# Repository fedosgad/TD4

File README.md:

# TD4
Schematics, PCBs and SystemVerilog simulation for extended version of TD4 CPU.

All circuit-related work done in KiCad.

Verilog file are (will be) under verilog/ folder

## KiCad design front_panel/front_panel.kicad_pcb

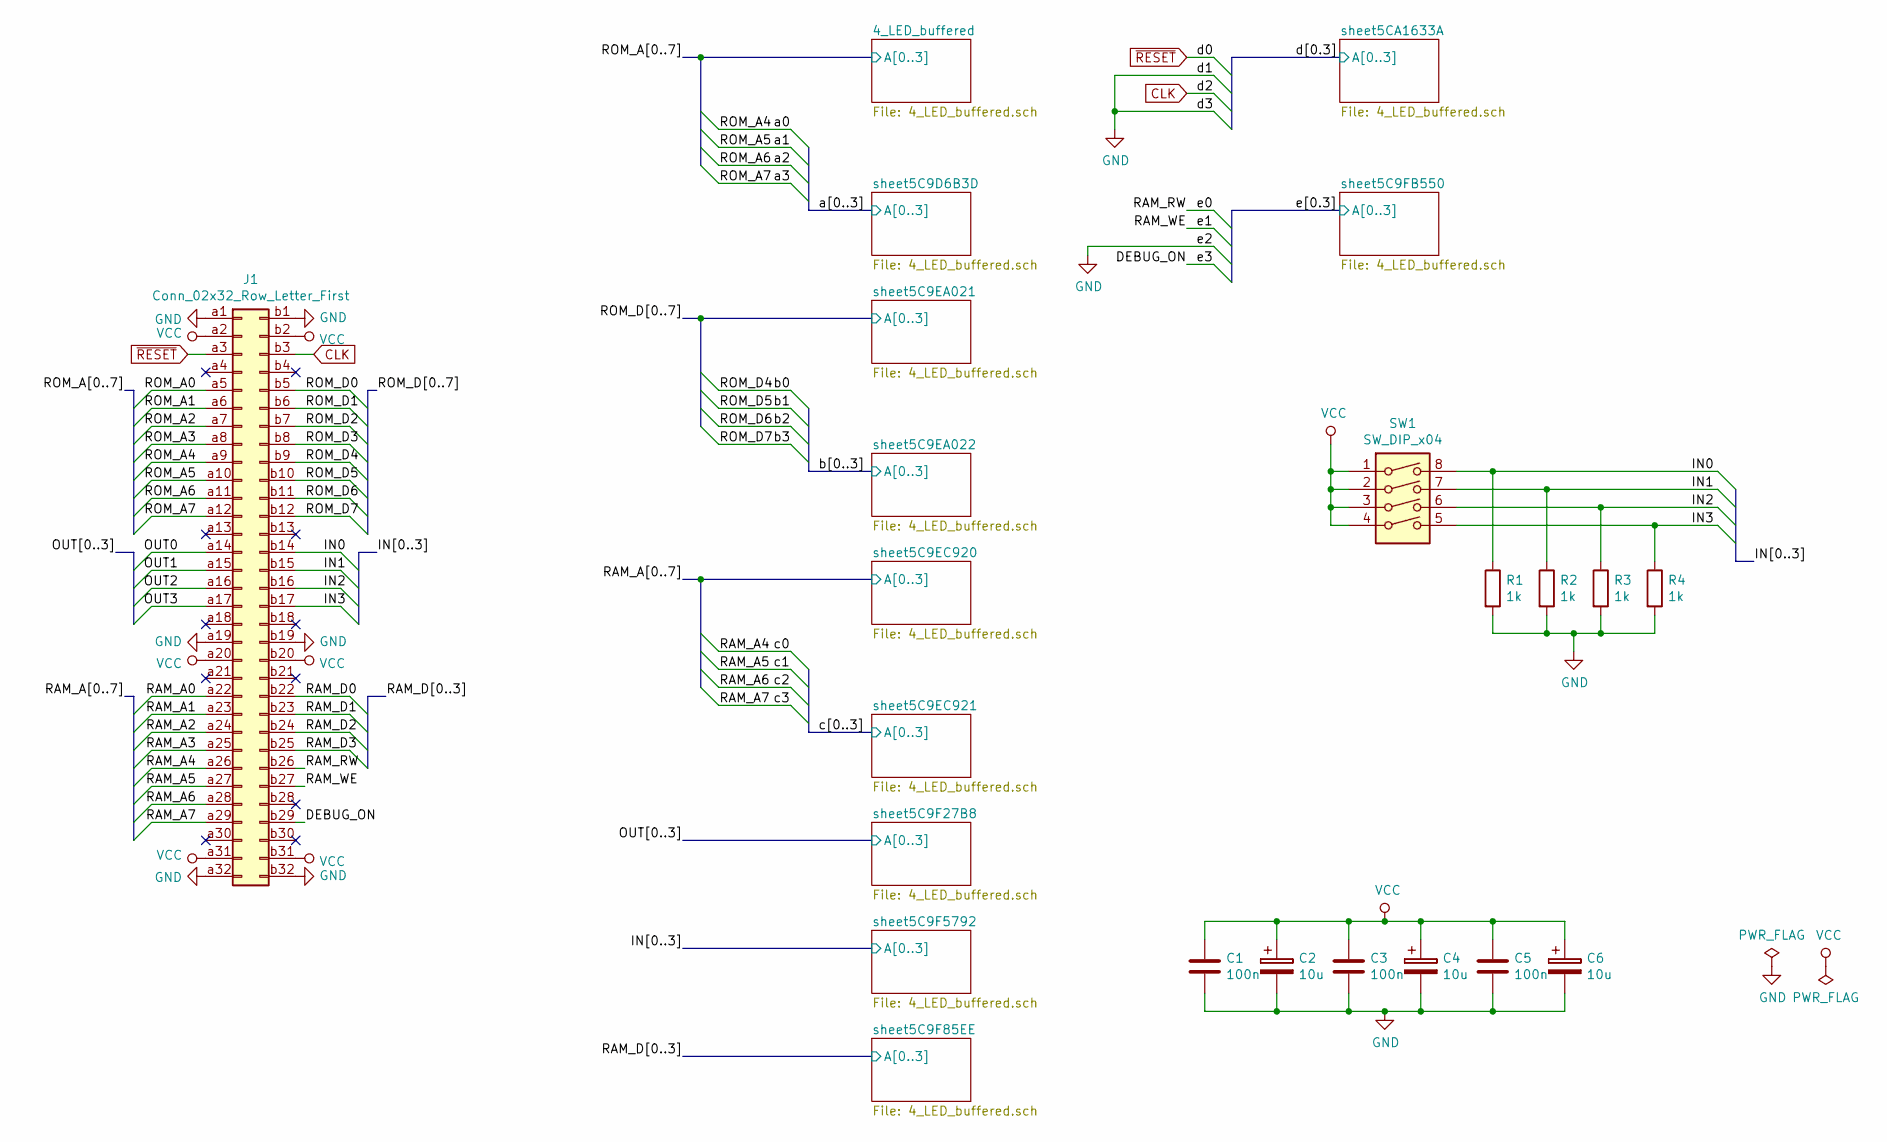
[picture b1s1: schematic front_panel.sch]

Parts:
C1, C3, C5: 100n; C_0805_2012Metric
C2, C4, C6: 10u; CP_EIA-3216-18_Kemet-A
J1: Conn_02x32_Row_Letter_First; DIN41612_B_2x32_Horizontal
R1, R2, R3, R4: 1k; R_0805_2012Metric
SW1: SW_DIP_x04; SW_DIP_SPSTx04_Slide_9.78x12.34mm_W7.62mm_P2.54mm

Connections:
/DEBUG_ON: J1.b29; also elsewhere on the board
/IN0: J1.b14, R1.1, SW1.8; also elsewhere on the board
/IN1: J1.b15, R2.1, SW1.7; also elsewhere on the board
/IN2: J1.b16, R3.1, SW1.6; also elsewhere on the board
/IN3: J1.b17, R4.1, SW1.5; also elsewhere on the board
/OUT0: J1.a14; also elsewhere on the board
/OUT1: J1.a15; also elsewhere on the board
/OUT2: J1.a16; also elsewhere on the board
/OUT3: J1.a17; also elsewhere on the board
/RAM_A0: J1.a22; also elsewhere on the board
/RAM_A1: J1.a23; also elsewhere on the board
/RAM_A2: J1.a24; also elsewhere on the board
/RAM_A3: J1.a25; also elsewhere on the board
/RAM_A4: J1.a26; also elsewhere on the board
/RAM_A5: J1.a27; also elsewhere on the board
/RAM_A6: J1.a28; also elsewhere on the board
/RAM_A7: J1.a29; also elsewhere on the board
/RAM_D0: J1.b22; also elsewhere on the board
/RAM_D1: J1.b23; also elsewhere on the board
/RAM_D2: J1.b24; also elsewhere on the board
/RAM_D3: J1.b25; also elsewhere on the board
/RAM_RW: J1.b26; also elsewhere on the board
/RAM_WE: J1.b27; also elsewhere on the board
/ROM_A0: J1.a5; also elsewhere on the board
/ROM_A1: J1.a6; also elsewhere on the board
/ROM_A2: J1.a7; also elsewhere on the board
/ROM_A3: J1.a8; also elsewhere on the board
/ROM_A4: J1.a9; also elsewhere on the board
/ROM_A5: J1.a10; also elsewhere on the board
/ROM_A6: J1.a11; also elsewhere on the board
/ROM_A7: J1.a12; also elsewhere on the board
/ROM_D0: J1.b5; also elsewhere on the board
/ROM_D1: J1.b6; also elsewhere on the board
/ROM_D2: J1.b7; also elsewhere on the board
/ROM_D3: J1.b8; also elsewhere on the board
/ROM_D4: J1.b9; also elsewhere on the board
/ROM_D5: J1.b10; also elsewhere on the board
/ROM_D6: J1.b11; also elsewhere on the board
/ROM_D7: J1.b12; also elsewhere on the board
CLK: J1.b3; also elsewhere on the board
GND: C1.2, C2.2, C3.2, C4.2, C5.2, C6.2, J1.a1, J1.a19, J1.a32, J1.b1, J1.b19, J1.b32, R1.2, R2.2, R3.2, R4.2; also elsewhere on the board
VCC: C1.1, C2.1, C3.1, C4.1, C5.1, C6.1, J1.a2, J1.a20, J1.a31, J1.b2, J1.b20, J1.b31, SW1.1, SW1.2, SW1.3, SW1.4; also elsewhere on the board
~RESET: J1.a3; also elsewhere on the board

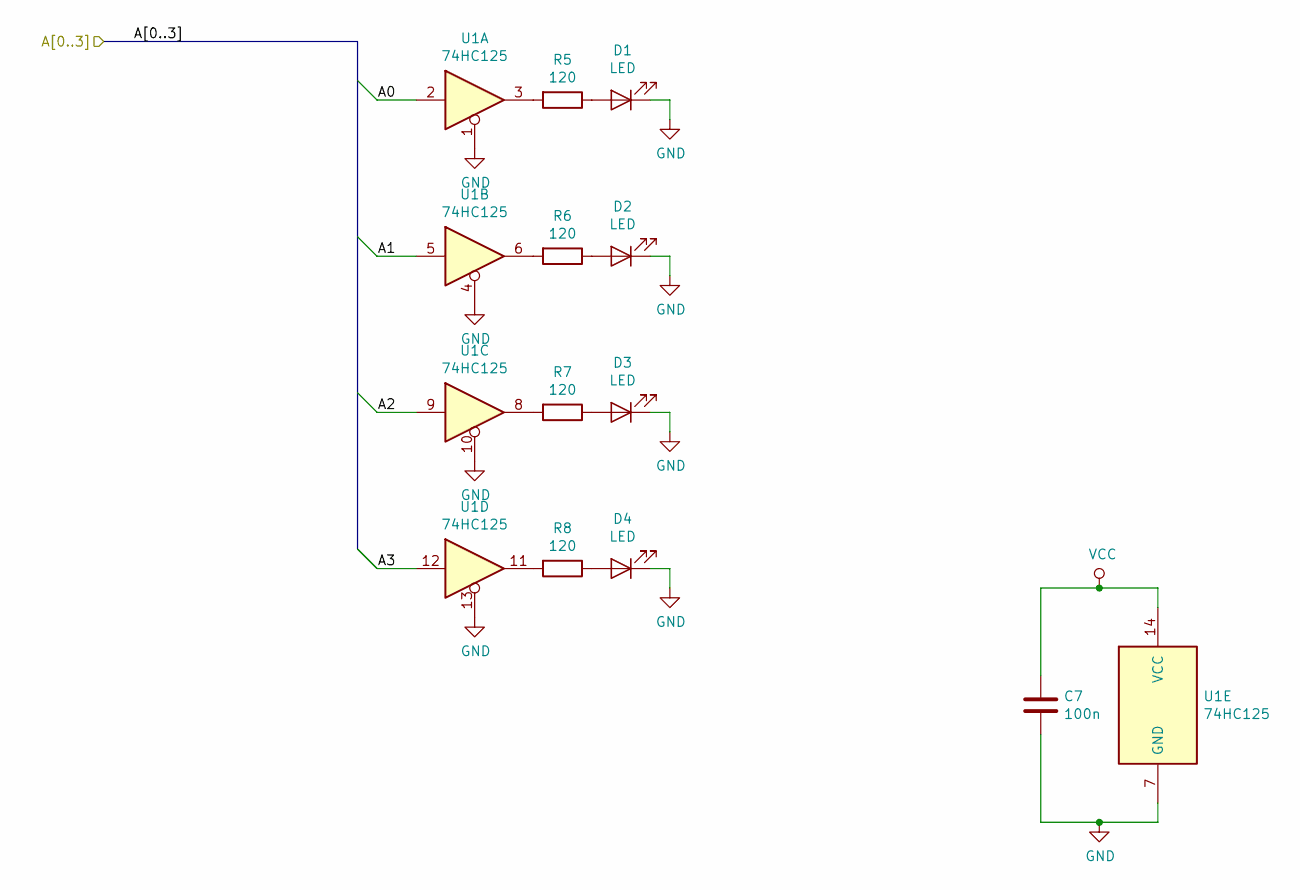
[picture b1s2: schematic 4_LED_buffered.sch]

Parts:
C7: 100n; C_0805_2012Metric
D1, D2, D3, D4: LED; LED_D5.0mm
R5, R6, R7, R8: 120; R_0805_2012Metric
U1: 74HC125; SOIC-14_3.9x8.7mm_P1.27mm

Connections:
/ROM_A0: U1.2; also elsewhere on the board
/ROM_A1: U1.5; also elsewhere on the board
/ROM_A2: U1.9; also elsewhere on the board
/ROM_A3: U1.12; also elsewhere on the board
GND: C7.2, D1.1 (K), D2.1 (K), D3.1 (K), D4.1 (K), U1.1, U1.4, U1.7 (GND), U1.10, U1.13; also elsewhere on the board
unnamed: D1.2 (A), R5.1
unnamed: D2.2 (A), R6.1
unnamed: D3.2 (A), R7.1
unnamed: D4.2 (A), R8.1
unnamed: R5.2, U1.3
unnamed: R6.2, U1.6
unnamed: R7.2, U1.8
unnamed: R8.2, U1.11
VCC: C7.1, U1.14 (VCC); also elsewhere on the board

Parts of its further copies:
C8, C9, C10, C11, C12, C13, C14, C15, C16, C17: 100n; C_0805_2012Metric
D5, D6, D7, D8, D9, D10, D11, D12, D13, D14, D15, D16, D17, D18, D19, D20, D21, D22, D23, D24, D25, D26, D27, D28, D29, D30, D31, D32, D33, D34, D35, D36, D37, D38, D39, D40, D41, D42, D43, D44: LED; LED_D5.0mm
R9, R10, R11, R12, R13, R14, R15, R16, R17, R18, R19, R20, R21, R22, R23, R24, R25, R26, R27, R28, R29, R30, R31, R32, R33, R34, R35, R36, R37, R38, R39, R40, R41, R42, R43, R44, R45, R46, R47, R48: 120; R_0805_2012Metric
U2, U3, U4, U5, U6, U7, U8, U9, U10, U11: 74HC125; SOIC-14_3.9x8.7mm_P1.27mm

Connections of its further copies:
/DEBUG_ON: U10.12; also elsewhere on the board
/IN0: U8.2; also elsewhere on the board
/IN1: U8.5; also elsewhere on the board
/IN2: U8.9; also elsewhere on the board
/IN3: U8.12; also elsewhere on the board
/OUT0: U7.2; also elsewhere on the board
/OUT1: U7.5; also elsewhere on the board
/OUT2: U7.9; also elsewhere on the board
/OUT3: U7.12; also elsewhere on the board
/RAM_A0: U5.2; also elsewhere on the board
/RAM_A1: U5.5; also elsewhere on the board
/RAM_A2: U5.9; also elsewhere on the board
/RAM_A3: U5.12; also elsewhere on the board
/RAM_A4: U6.2; also elsewhere on the board
/RAM_A5: U6.5; also elsewhere on the board
/RAM_A6: U6.9; also elsewhere on the board
/RAM_A7: U6.12; also elsewhere on the board
/RAM_D0: U9.2; also elsewhere on the board
/RAM_D1: U9.5; also elsewhere on the board
/RAM_D2: U9.9; also elsewhere on the board
/RAM_D3: U9.12; also elsewhere on the board
/RAM_RW: U10.2; also elsewhere on the board
/RAM_WE: U10.5; also elsewhere on the board
/ROM_A4: U2.2; also elsewhere on the board
/ROM_A5: U2.5; also elsewhere on the board
/ROM_A6: U2.9; also elsewhere on the board
/ROM_A7: U2.12; also elsewhere on the board
/ROM_D0: U3.2; also elsewhere on the board
/ROM_D1: U3.5; also elsewhere on the board
/ROM_D2: U3.9; also elsewhere on the board
/ROM_D3: U3.12; also elsewhere on the board
/ROM_D4: U4.2; also elsewhere on the board
/ROM_D5: U4.5; also elsewhere on the board
/ROM_D6: U4.9; also elsewhere on the board
/ROM_D7: U4.12; also elsewhere on the board
CLK: U11.9; also elsewhere on the board
GND: C8.2, C9.2, C10.2, C11.2, C12.2, C13.2, C14.2, C15.2, C16.2, C17.2, D5.1 (K), D6.1 (K), D7.1 (K), D8.1 (K), D9.1 (K), D10.1 (K), D11.1 (K), D12.1 (K), D13.1 (K), D14.1 (K), D15.1 (K), D16.1 (K), D17.1 (K), D18.1 (K), D19.1 (K), D20.1 (K), D21.1 (K), D22.1 (K), D23.1 (K), D24.1 (K), D25.1 (K), D26.1 (K), D27.1 (K), D28.1 (K), D29.1 (K), D30.1 (K), D31.1 (K), D32.1 (K), D33.1 (K), D34.1 (K), D35.1 (K), D36.1 (K), D37.1 (K), D38.1 (K), D39.1 (K), D40.1 (K), D41.1 (K), D42.1 (K), D43.1 (K), D44.1 (K), U2.1, U2.4, U2.7 (GND), U2.10, U2.13, U3.1, U3.4, U3.7 (GND), U3.10, U3.13, U4.1, U4.4, U4.7 (GND), U4.10, U4.13, U5.1, U5.4, U5.7 (GND), U5.10, U5.13, U6.1, U6.4, U6.7 (GND), U6.10, U6.13, U7.1, U7.4, U7.7 (GND), U7.10, U7.13, U8.1, U8.4, U8.7 (GND), U8.10, U8.13, U9.1, U9.4, U9.7 (GND), U9.10, U9.13, U10.1, U10.4, U10.7 (GND), U10.9, U10.10, U10.13, U11.1, U11.4, U11.5, U11.7 (GND), U11.10, U11.12, U11.13; also elsewhere on the board
unnamed: D5.2 (A), R9.1
unnamed: D6.2 (A), R10.1
unnamed: D7.2 (A), R11.1
unnamed: D8.2 (A), R12.1
unnamed: D9.2 (A), R13.1
unnamed: D10.2 (A), R14.1
unnamed: D11.2 (A), R15.1
unnamed: D12.2 (A), R16.1
unnamed: D13.2 (A), R17.1
unnamed: D14.2 (A), R18.1
unnamed: D15.2 (A), R19.1
unnamed: D16.2 (A), R20.1
unnamed: D17.2 (A), R21.1
unnamed: D18.2 (A), R22.1
unnamed: D19.2 (A), R23.1
unnamed: D20.2 (A), R24.1
unnamed: D21.2 (A), R25.1
unnamed: D22.2 (A), R26.1
unnamed: D23.2 (A), R27.1
unnamed: D24.2 (A), R28.1
unnamed: D25.2 (A), R29.1
unnamed: D26.2 (A), R30.1
unnamed: D27.2 (A), R31.1
unnamed: D28.2 (A), R32.1
unnamed: D29.2 (A), R33.1
unnamed: D30.2 (A), R34.1
unnamed: D31.2 (A), R35.1
unnamed: D32.2 (A), R36.1
unnamed: D33.2 (A), R37.1
unnamed: D34.2 (A), R38.1
unnamed: D35.2 (A), R39.1
unnamed: D36.2 (A), R40.1
unnamed: D37.2 (A), R41.1
unnamed: D38.2 (A), R42.1
unnamed: D39.2 (A), R43.1
unnamed: D40.2 (A), R44.1
unnamed: D41.2 (A), R45.1
unnamed: D42.2 (A), R46.1
unnamed: D43.2 (A), R47.1
unnamed: D44.2 (A), R48.1
unnamed: R9.2, U2.3
unnamed: R10.2, U2.6
unnamed: R11.2, U2.8
unnamed: R12.2, U2.11
unnamed: R13.2, U3.3
unnamed: R14.2, U3.6
unnamed: R15.2, U3.8
unnamed: R16.2, U3.11
unnamed: R17.2, U4.3
unnamed: R18.2, U4.6
unnamed: R19.2, U4.8
unnamed: R20.2, U4.11
unnamed: R21.2, U5.3
unnamed: R22.2, U5.6
unnamed: R23.2, U5.8
unnamed: R24.2, U5.11
unnamed: R25.2, U6.3
unnamed: R26.2, U6.6
unnamed: R27.2, U6.8
unnamed: R28.2, U6.11
unnamed: R29.2, U7.3
unnamed: R30.2, U7.6
unnamed: R31.2, U7.8
unnamed: R32.2, U7.11
unnamed: R33.2, U8.3
unnamed: R34.2, U8.6
unnamed: R35.2, U8.8
unnamed: R36.2, U8.11
unnamed: R37.2, U9.3
unnamed: R38.2, U9.6
unnamed: R39.2, U9.8
unnamed: R40.2, U9.11
unnamed: R41.2, U10.3
unnamed: R42.2, U10.6
unnamed: R43.2, U10.8
unnamed: R44.2, U10.11
unnamed: R45.2, U11.3
unnamed: R46.2, U11.6
unnamed: R47.2, U11.8
unnamed: R48.2, U11.11
VCC: C8.1, C9.1, C10.1, C11.1, C12.1, C13.1, C14.1, C15.1, C16.1, C17.1, U2.14 (VCC), U3.14 (VCC), U4.14 (VCC), U5.14 (VCC), U6.14 (VCC), U7.14 (VCC), U8.14 (VCC), U9.14 (VCC), U10.14 (VCC), U11.14 (VCC); also elsewhere on the board
~RESET: U11.2; also elsewhere on the board

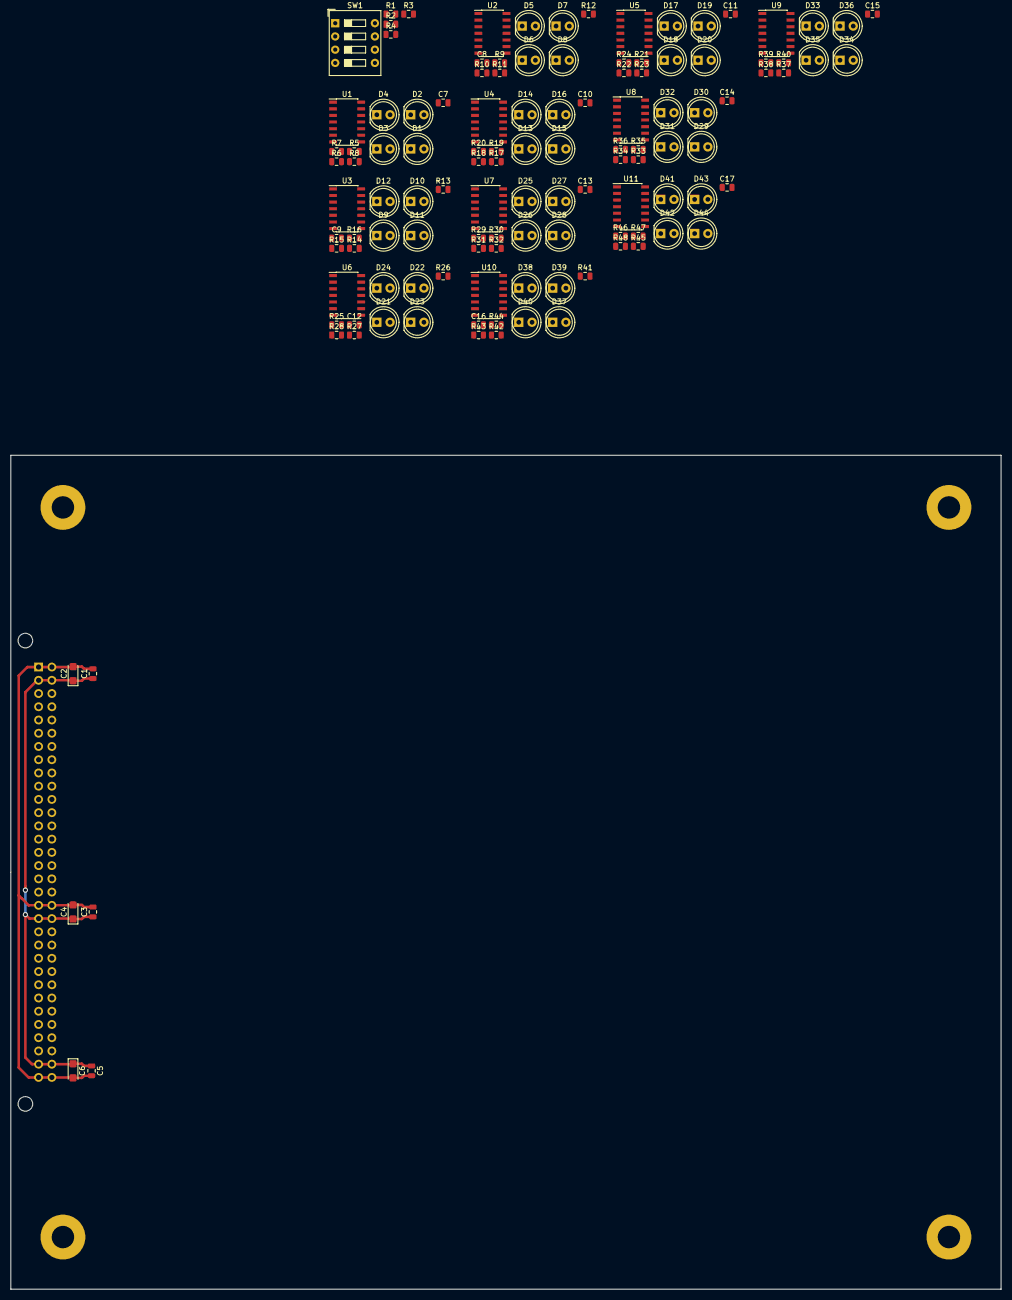
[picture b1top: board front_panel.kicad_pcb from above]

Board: 2 copper layers, 190.0 x 160.0 mm, 122 parts (1 on the bottom side), 131 nets.

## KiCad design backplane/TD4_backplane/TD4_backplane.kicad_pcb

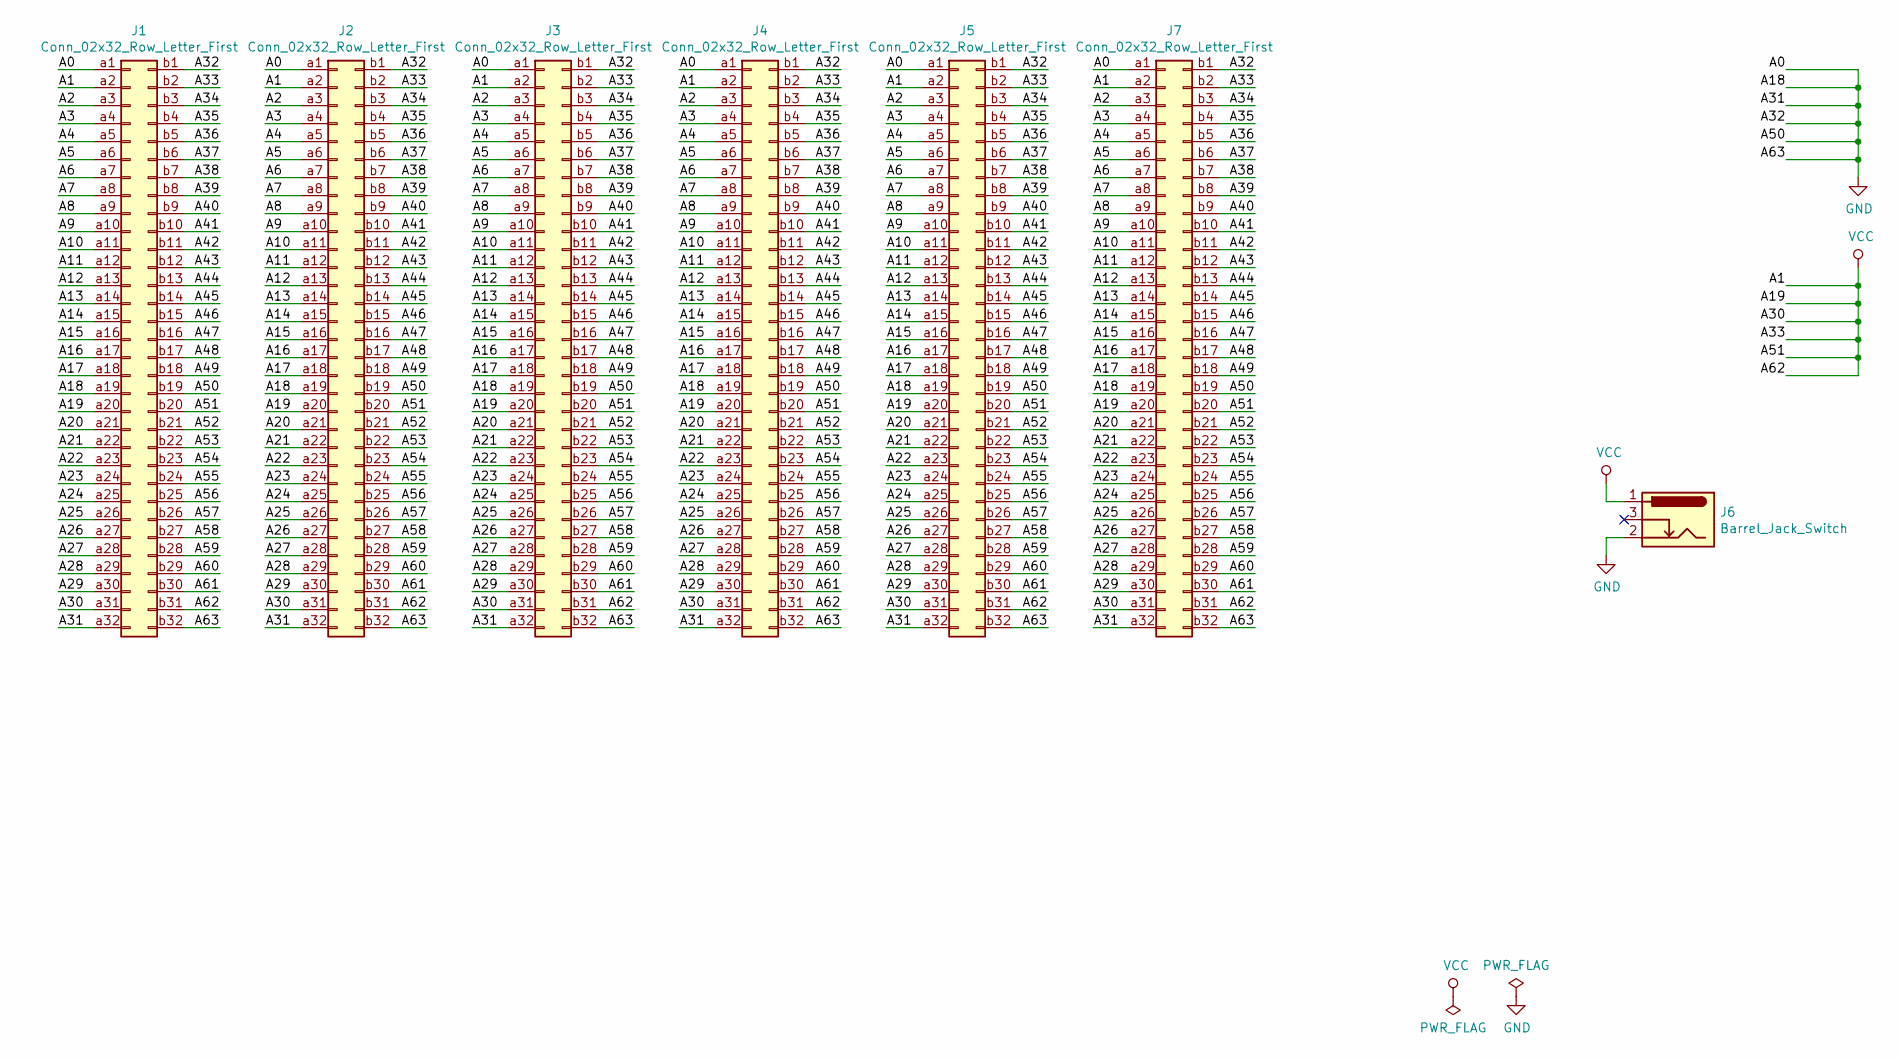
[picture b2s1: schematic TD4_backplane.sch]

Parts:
J1, J2, J3, J4, J5, J7: Conn_02x32_Row_Letter_First; DIN41612_B_2x32_Vertical
J6: Barrel_Jack_Switch; BarrelJack_Horizontal

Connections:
/A2: J1.a3, J2.a3, J3.a3, J4.a3, J5.a3, J7.a3
/A3: J1.a4, J2.a4, J3.a4, J4.a4, J5.a4, J7.a4
/A4: J1.a5, J2.a5, J3.a5, J4.a5, J5.a5, J7.a5
/A5: J1.a6, J2.a6, J3.a6, J4.a6, J5.a6, J7.a6
/A6: J1.a7, J2.a7, J3.a7, J4.a7, J5.a7, J7.a7
/A7: J1.a8, J2.a8, J3.a8, J4.a8, J5.a8, J7.a8
/A8: J1.a9, J2.a9, J3.a9, J4.a9, J5.a9, J7.a9
/A9: J1.a10, J2.a10, J3.a10, J4.a10, J5.a10, J7.a10
/A10: J1.a11, J2.a11, J3.a11, J4.a11, J5.a11, J7.a11
/A11: J1.a12, J2.a12, J3.a12, J4.a12, J5.a12, J7.a12
/A12: J1.a13, J2.a13, J3.a13, J4.a13, J5.a13, J7.a13
/A13: J1.a14, J2.a14, J3.a14, J4.a14, J5.a14, J7.a14
/A14: J1.a15, J2.a15, J3.a15, J4.a15, J5.a15, J7.a15
/A15: J1.a16, J2.a16, J3.a16, J4.a16, J5.a16, J7.a16
/A16: J1.a17, J2.a17, J3.a17, J4.a17, J5.a17, J7.a17
/A17: J1.a18, J2.a18, J3.a18, J4.a18, J5.a18, J7.a18
/A20: J1.a21, J2.a21, J3.a21, J4.a21, J5.a21, J7.a21
/A21: J1.a22, J2.a22, J3.a22, J4.a22, J5.a22, J7.a22
/A22: J1.a23, J2.a23, J3.a23, J4.a23, J5.a23, J7.a23
/A23: J1.a24, J2.a24, J3.a24, J4.a24, J5.a24, J7.a24
/A24: J1.a25, J2.a25, J3.a25, J4.a25, J5.a25, J7.a25
/A25: J1.a26, J2.a26, J3.a26, J4.a26, J5.a26, J7.a26
/A26: J1.a27, J2.a27, J3.a27, J4.a27, J5.a27, J7.a27
/A27: J1.a28, J2.a28, J3.a28, J4.a28, J5.a28, J7.a28
/A28: J1.a29, J2.a29, J3.a29, J4.a29, J5.a29, J7.a29
/A29: J1.a30, J2.a30, J3.a30, J4.a30, J5.a30, J7.a30
/A34: J1.b3, J2.b3, J3.b3, J4.b3, J5.b3, J7.b3
/A35: J1.b4, J2.b4, J3.b4, J4.b4, J5.b4, J7.b4
/A36: J1.b5, J2.b5, J3.b5, J4.b5, J5.b5, J7.b5
/A37: J1.b6, J2.b6, J3.b6, J4.b6, J5.b6, J7.b6
/A38: J1.b7, J2.b7, J3.b7, J4.b7, J5.b7, J7.b7
/A39: J1.b8, J2.b8, J3.b8, J4.b8, J5.b8, J7.b8
/A40: J1.b9, J2.b9, J3.b9, J4.b9, J5.b9, J7.b9
/A41: J1.b10, J2.b10, J3.b10, J4.b10, J5.b10, J7.b10
/A42: J1.b11, J2.b11, J3.b11, J4.b11, J5.b11, J7.b11
/A43: J1.b12, J2.b12, J3.b12, J4.b12, J5.b12, J7.b12
/A44: J1.b13, J2.b13, J3.b13, J4.b13, J5.b13, J7.b13
/A45: J1.b14, J2.b14, J3.b14, J4.b14, J5.b14, J7.b14
/A46: J1.b15, J2.b15, J3.b15, J4.b15, J5.b15, J7.b15
/A47: J1.b16, J2.b16, J3.b16, J4.b16, J5.b16, J7.b16
/A48: J1.b17, J2.b17, J3.b17, J4.b17, J5.b17, J7.b17
/A49: J1.b18, J2.b18, J3.b18, J4.b18, J5.b18, J7.b18
/A52: J1.b21, J2.b21, J3.b21, J4.b21, J5.b21, J7.b21
/A53: J1.b22, J2.b22, J3.b22, J4.b22, J5.b22, J7.b22
/A54: J1.b23, J2.b23, J3.b23, J4.b23, J5.b23, J7.b23
/A55: J1.b24, J2.b24, J3.b24, J4.b24, J5.b24, J7.b24
/A56: J1.b25, J2.b25, J3.b25, J4.b25, J5.b25, J7.b25
/A57: J1.b26, J2.b26, J3.b26, J4.b26, J5.b26, J7.b26
/A58: J1.b27, J2.b27, J3.b27, J4.b27, J5.b27, J7.b27
/A59: J1.b28, J2.b28, J3.b28, J4.b28, J5.b28, J7.b28
/A60: J1.b29, J2.b29, J3.b29, J4.b29, J5.b29, J7.b29
/A61: J1.b30, J2.b30, J3.b30, J4.b30, J5.b30, J7.b30
GND: J1.a1, J1.a19, J1.a32, J1.b1, J1.b19, J1.b32, J2.a1, J2.a19, J2.a32, J2.b1, J2.b19, J2.b32, J3.a1, J3.a19, J3.a32, J3.b1, J3.b19, J3.b32, J4.a1, J4.a19, J4.a32, J4.b1, J4.b19, J4.b32, J5.a1, J5.a19, J5.a32, J5.b1, J5.b19, J5.b32, J6.2, J7.a1, J7.a19, J7.a32, J7.b1, J7.b19, J7.b32
VCC: J1.a2, J1.a20, J1.a31, J1.b2, J1.b20, J1.b31, J2.a2, J2.a20, J2.a31, J2.b2, J2.b20, J2.b31, J3.a2, J3.a20, J3.a31, J3.b2, J3.b20, J3.b31, J4.a2, J4.a20, J4.a31, J4.b2, J4.b20, J4.b31, J5.a2, J5.a20, J5.a31, J5.b2, J5.b20, J5.b31, J6.1, J7.a2, J7.a20, J7.a31, J7.b2, J7.b20, J7.b31

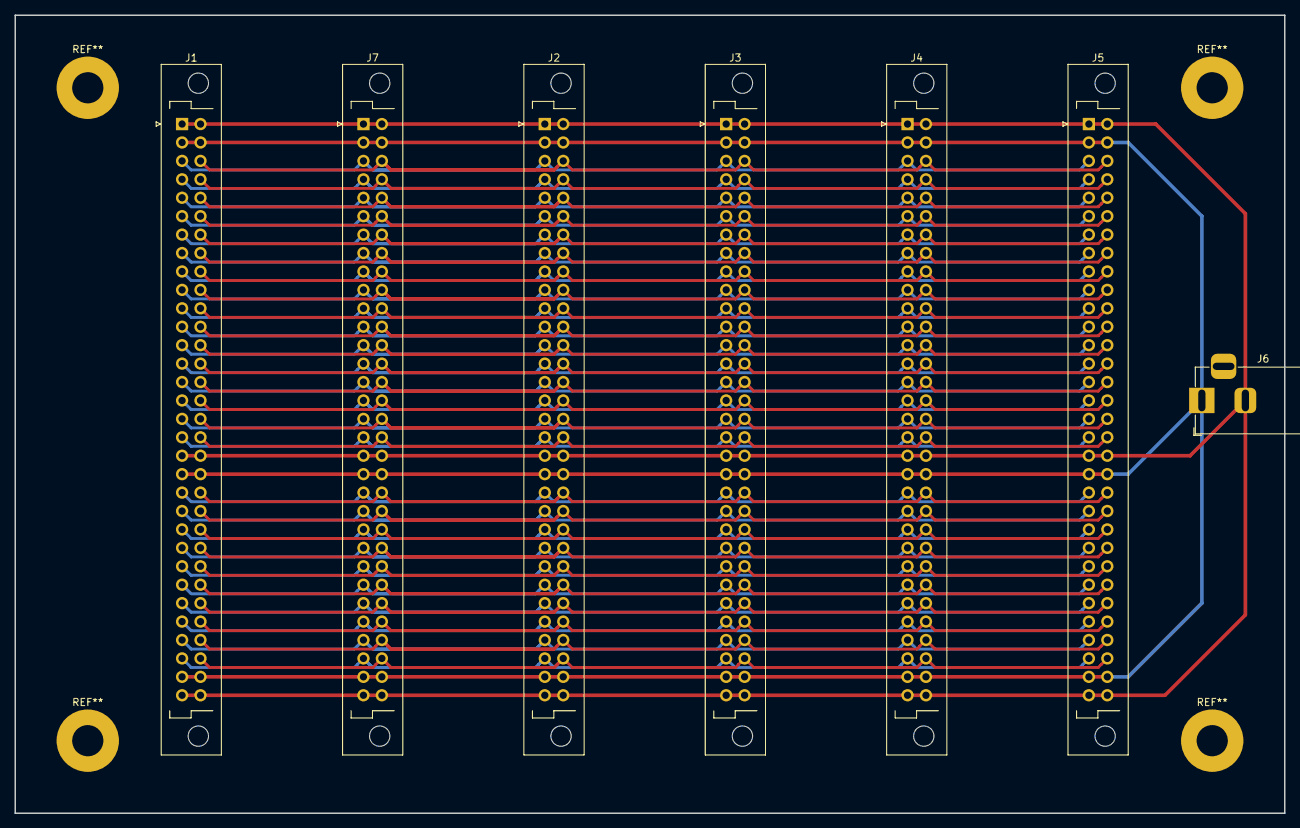
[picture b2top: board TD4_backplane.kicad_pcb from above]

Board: 2 copper layers, 175.0 x 110.0 mm, 7 parts (0 on the bottom side), 54 nets.

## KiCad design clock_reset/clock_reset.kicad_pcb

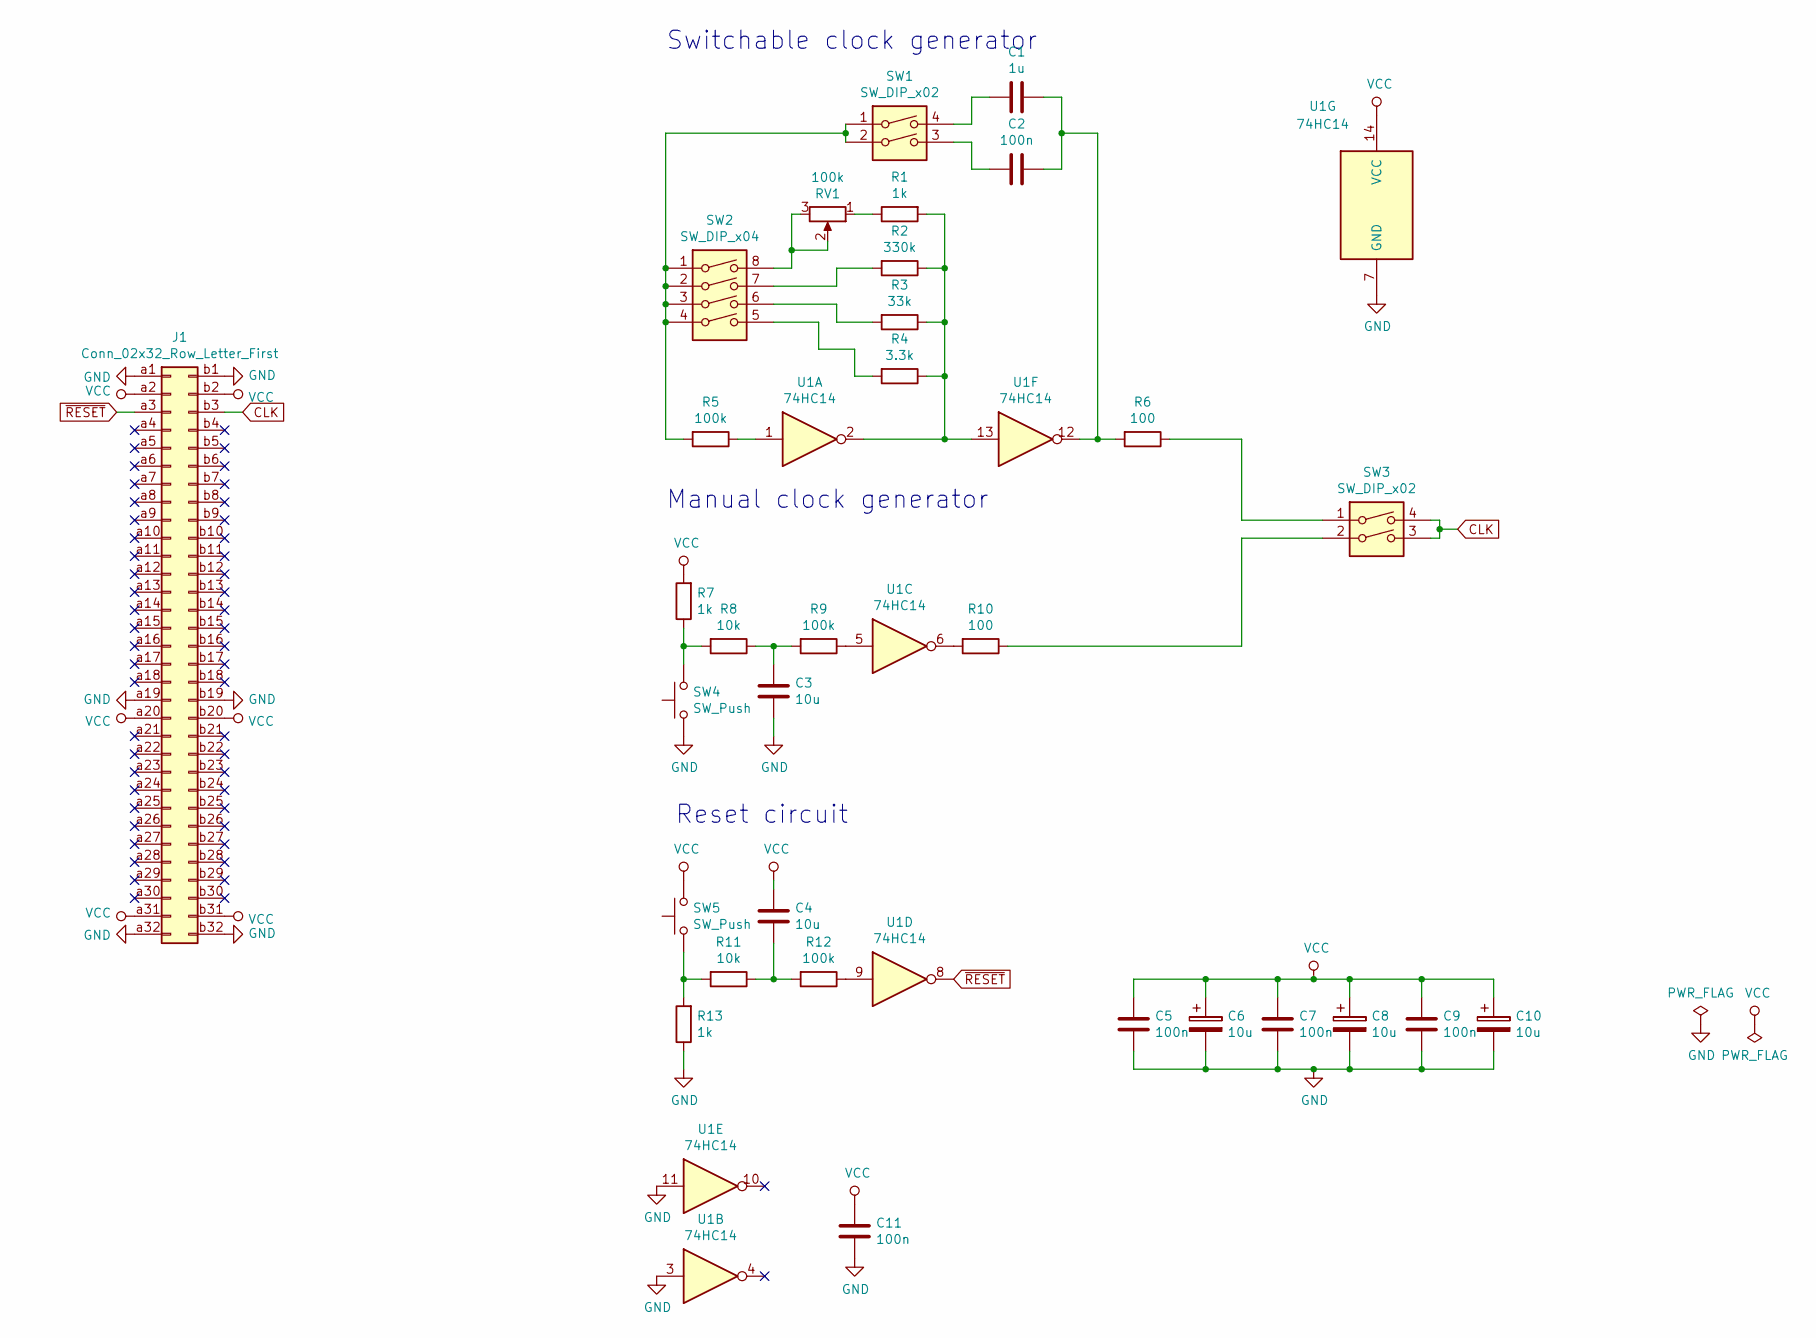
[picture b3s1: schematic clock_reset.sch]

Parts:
C1: 1u; C_0805_2012Metric
C2, C5, C7, C9, C11: 100n; C_0805_2012Metric
C3, C4, C6, C8, C10: 10u; CP_EIA-3216-18_Kemet-A
J1: Conn_02x32_Row_Letter_First; DIN41612_B_2x32_Horizontal
R1, R7, R13: 1k; R_0805_2012Metric
R2: 330k; R_0805_2012Metric
R3: 33k; R_0805_2012Metric
R4: 3.3k; R_0805_2012Metric
R5, R9, R12: 100k; R_0805_2012Metric
R6, R10: 100; R_0805_2012Metric
R8, R11: 10k; R_0805_2012Metric
RV1: 100k; Potentiometer_Piher_T-16H_Single_Horizontal
SW1, SW3: SW_DIP_x02; SW_DIP_SPSTx02_Slide_9.78x7.26mm_W7.62mm_P2.54mm
SW2: SW_DIP_x04; SW_DIP_SPSTx04_Slide_9.78x12.34mm_W7.62mm_P2.54mm
SW4, SW5: SW_Push; SW_PUSH_6mm
U1: 74HC14; SOIC-14_3.9x8.7mm_P1.27mm

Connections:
CLK: J1.b3, SW3.3, SW3.4
GND: C3.2, C5.2, C6.2, C7.2, C8.2, C9.2, C10.2, C11.2, J1.a1, J1.a19, J1.a32, J1.b1, J1.b19, J1.b32, R13.1, SW4.1, U1.3, U1.7 (GND), U1.11
unnamed: C1.1, C2.1, R6.2, U1.12
unnamed: C1.2, SW1.4
unnamed: C2.2, SW1.3
unnamed: C3.1, R8.1, R9.2
unnamed: C4.2, R11.1, R12.2
unnamed: R1.1, RV1.1
unnamed: R1.2, R2.1, R3.1, R4.1, U1.2, U1.13
unnamed: R2.2, SW2.7
unnamed: R3.2, SW2.6
unnamed: R4.2, SW2.5
unnamed: R5.1, U1.1
unnamed: R5.2, SW1.1, SW1.2, SW2.1, SW2.2, SW2.3, SW2.4
unnamed: R6.1, SW3.1
unnamed: R7.1, R8.2, SW4.2
unnamed: R9.1, U1.5
unnamed: R10.1, SW3.2
unnamed: R10.2, U1.6
unnamed: R11.2, R13.2, SW5.1
unnamed: R12.1, U1.9
unnamed: RV1.2, RV1.3, SW2.8
VCC: C4.1, C5.1, C6.1, C7.1, C8.1, C9.1, C10.1, C11.1, J1.a2, J1.a20, J1.a31, J1.b2, J1.b20, J1.b31, R7.2, SW5.2, U1.14 (VCC)
~RESET: J1.a3, U1.8

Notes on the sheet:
Switchable clock generator
Manual clock generator
Reset circuit

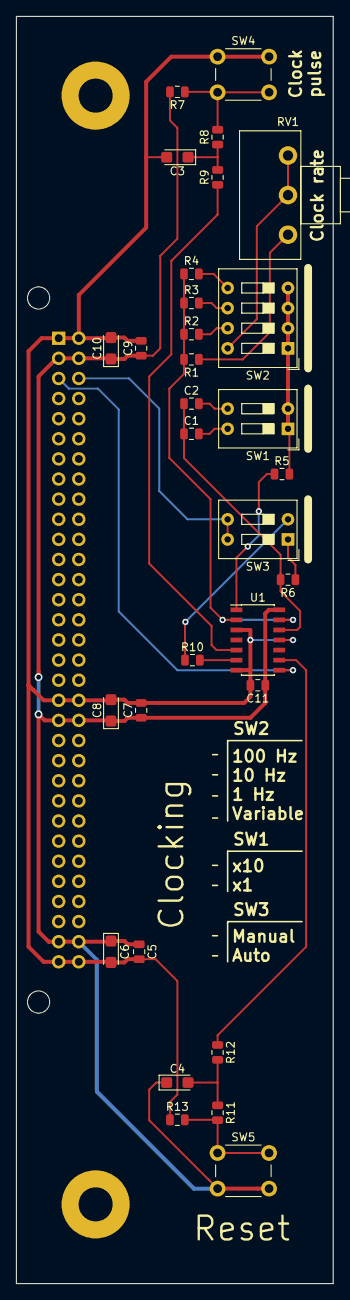
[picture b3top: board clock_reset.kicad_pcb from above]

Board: 2 copper layers, 40.0 x 160.0 mm, 32 parts (1 on the bottom side), 24 nets.

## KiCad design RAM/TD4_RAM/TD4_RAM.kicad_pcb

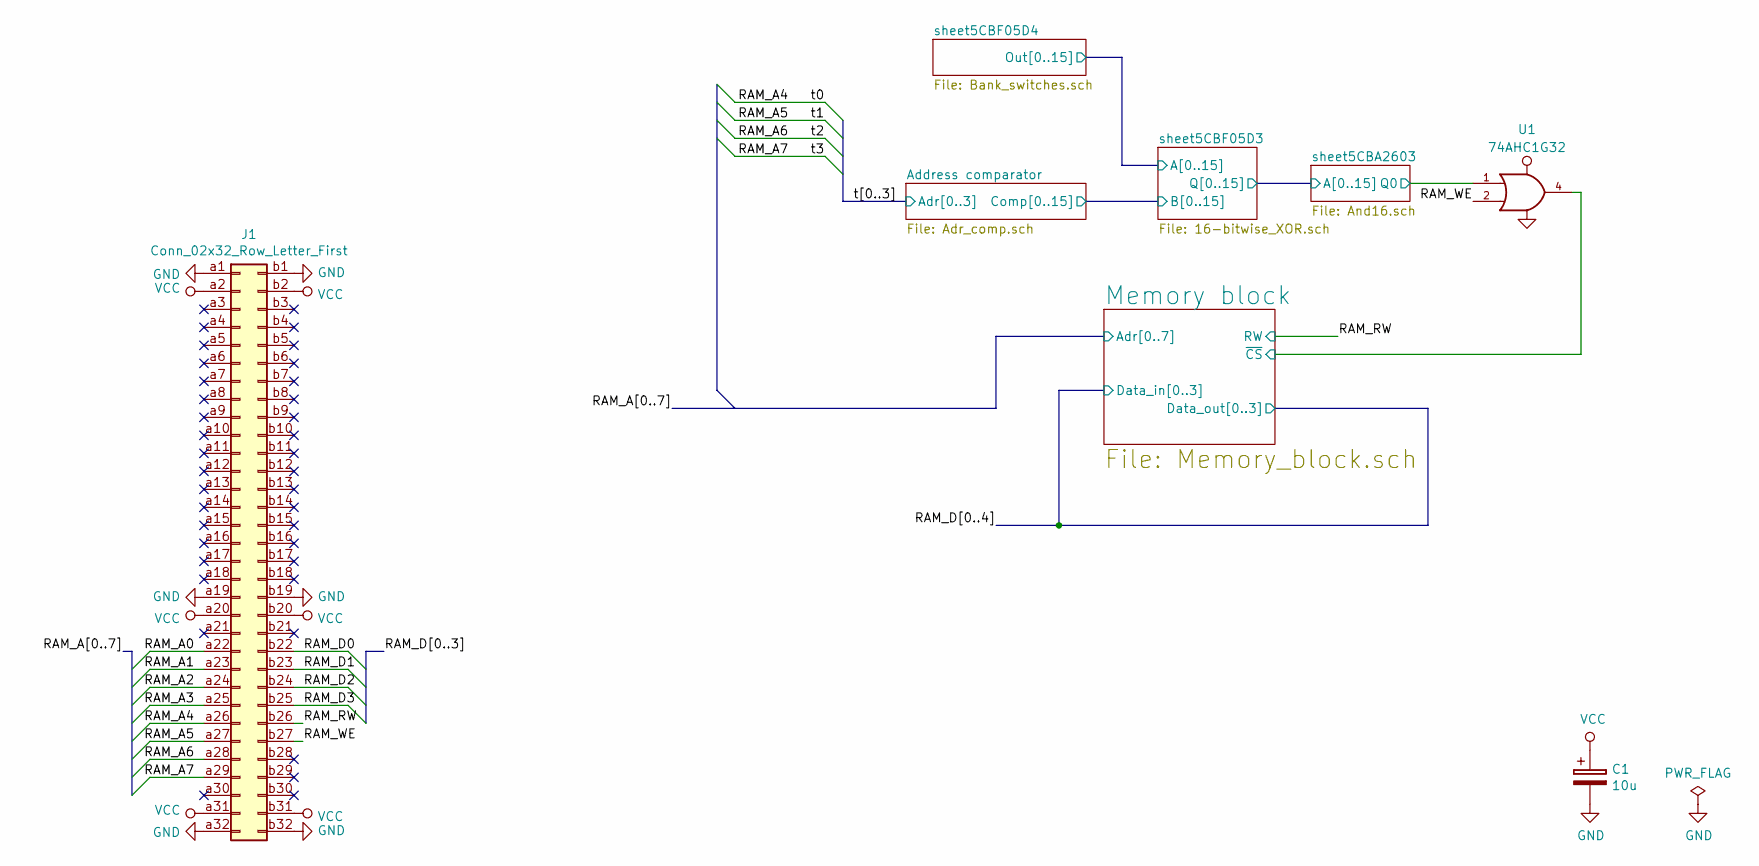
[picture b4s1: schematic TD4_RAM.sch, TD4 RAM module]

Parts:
C1: 10u; CP_EIA-3216-18_Kemet-A
J1: Conn_02x32_Row_Letter_First; DIN41612_B_2x32_Horizontal
U1: 74AHC1G32; SOT-23-5

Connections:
/Memory block/~CS: U1.4; also elsewhere on the board
/RAM_A0: J1.a22; also elsewhere on the board
/RAM_A1: J1.a23; also elsewhere on the board
/RAM_A2: J1.a24; also elsewhere on the board
/RAM_A3: J1.a25; also elsewhere on the board
/RAM_A4: J1.a26; also elsewhere on the board
/RAM_A5: J1.a27; also elsewhere on the board
/RAM_A6: J1.a28; also elsewhere on the board
/RAM_A7: J1.a29; also elsewhere on the board
/RAM_RW: J1.b26; also elsewhere on the board
/RAM_WE: J1.b27, U1.2
/sheet5CBA2603/Q0: U1.1; also elsewhere on the board
VCC: C1.1, J1.a2, J1.a20, J1.a31, J1.b2, J1.b20, J1.b31, U1.5 (VCC); also elsewhere on the board
